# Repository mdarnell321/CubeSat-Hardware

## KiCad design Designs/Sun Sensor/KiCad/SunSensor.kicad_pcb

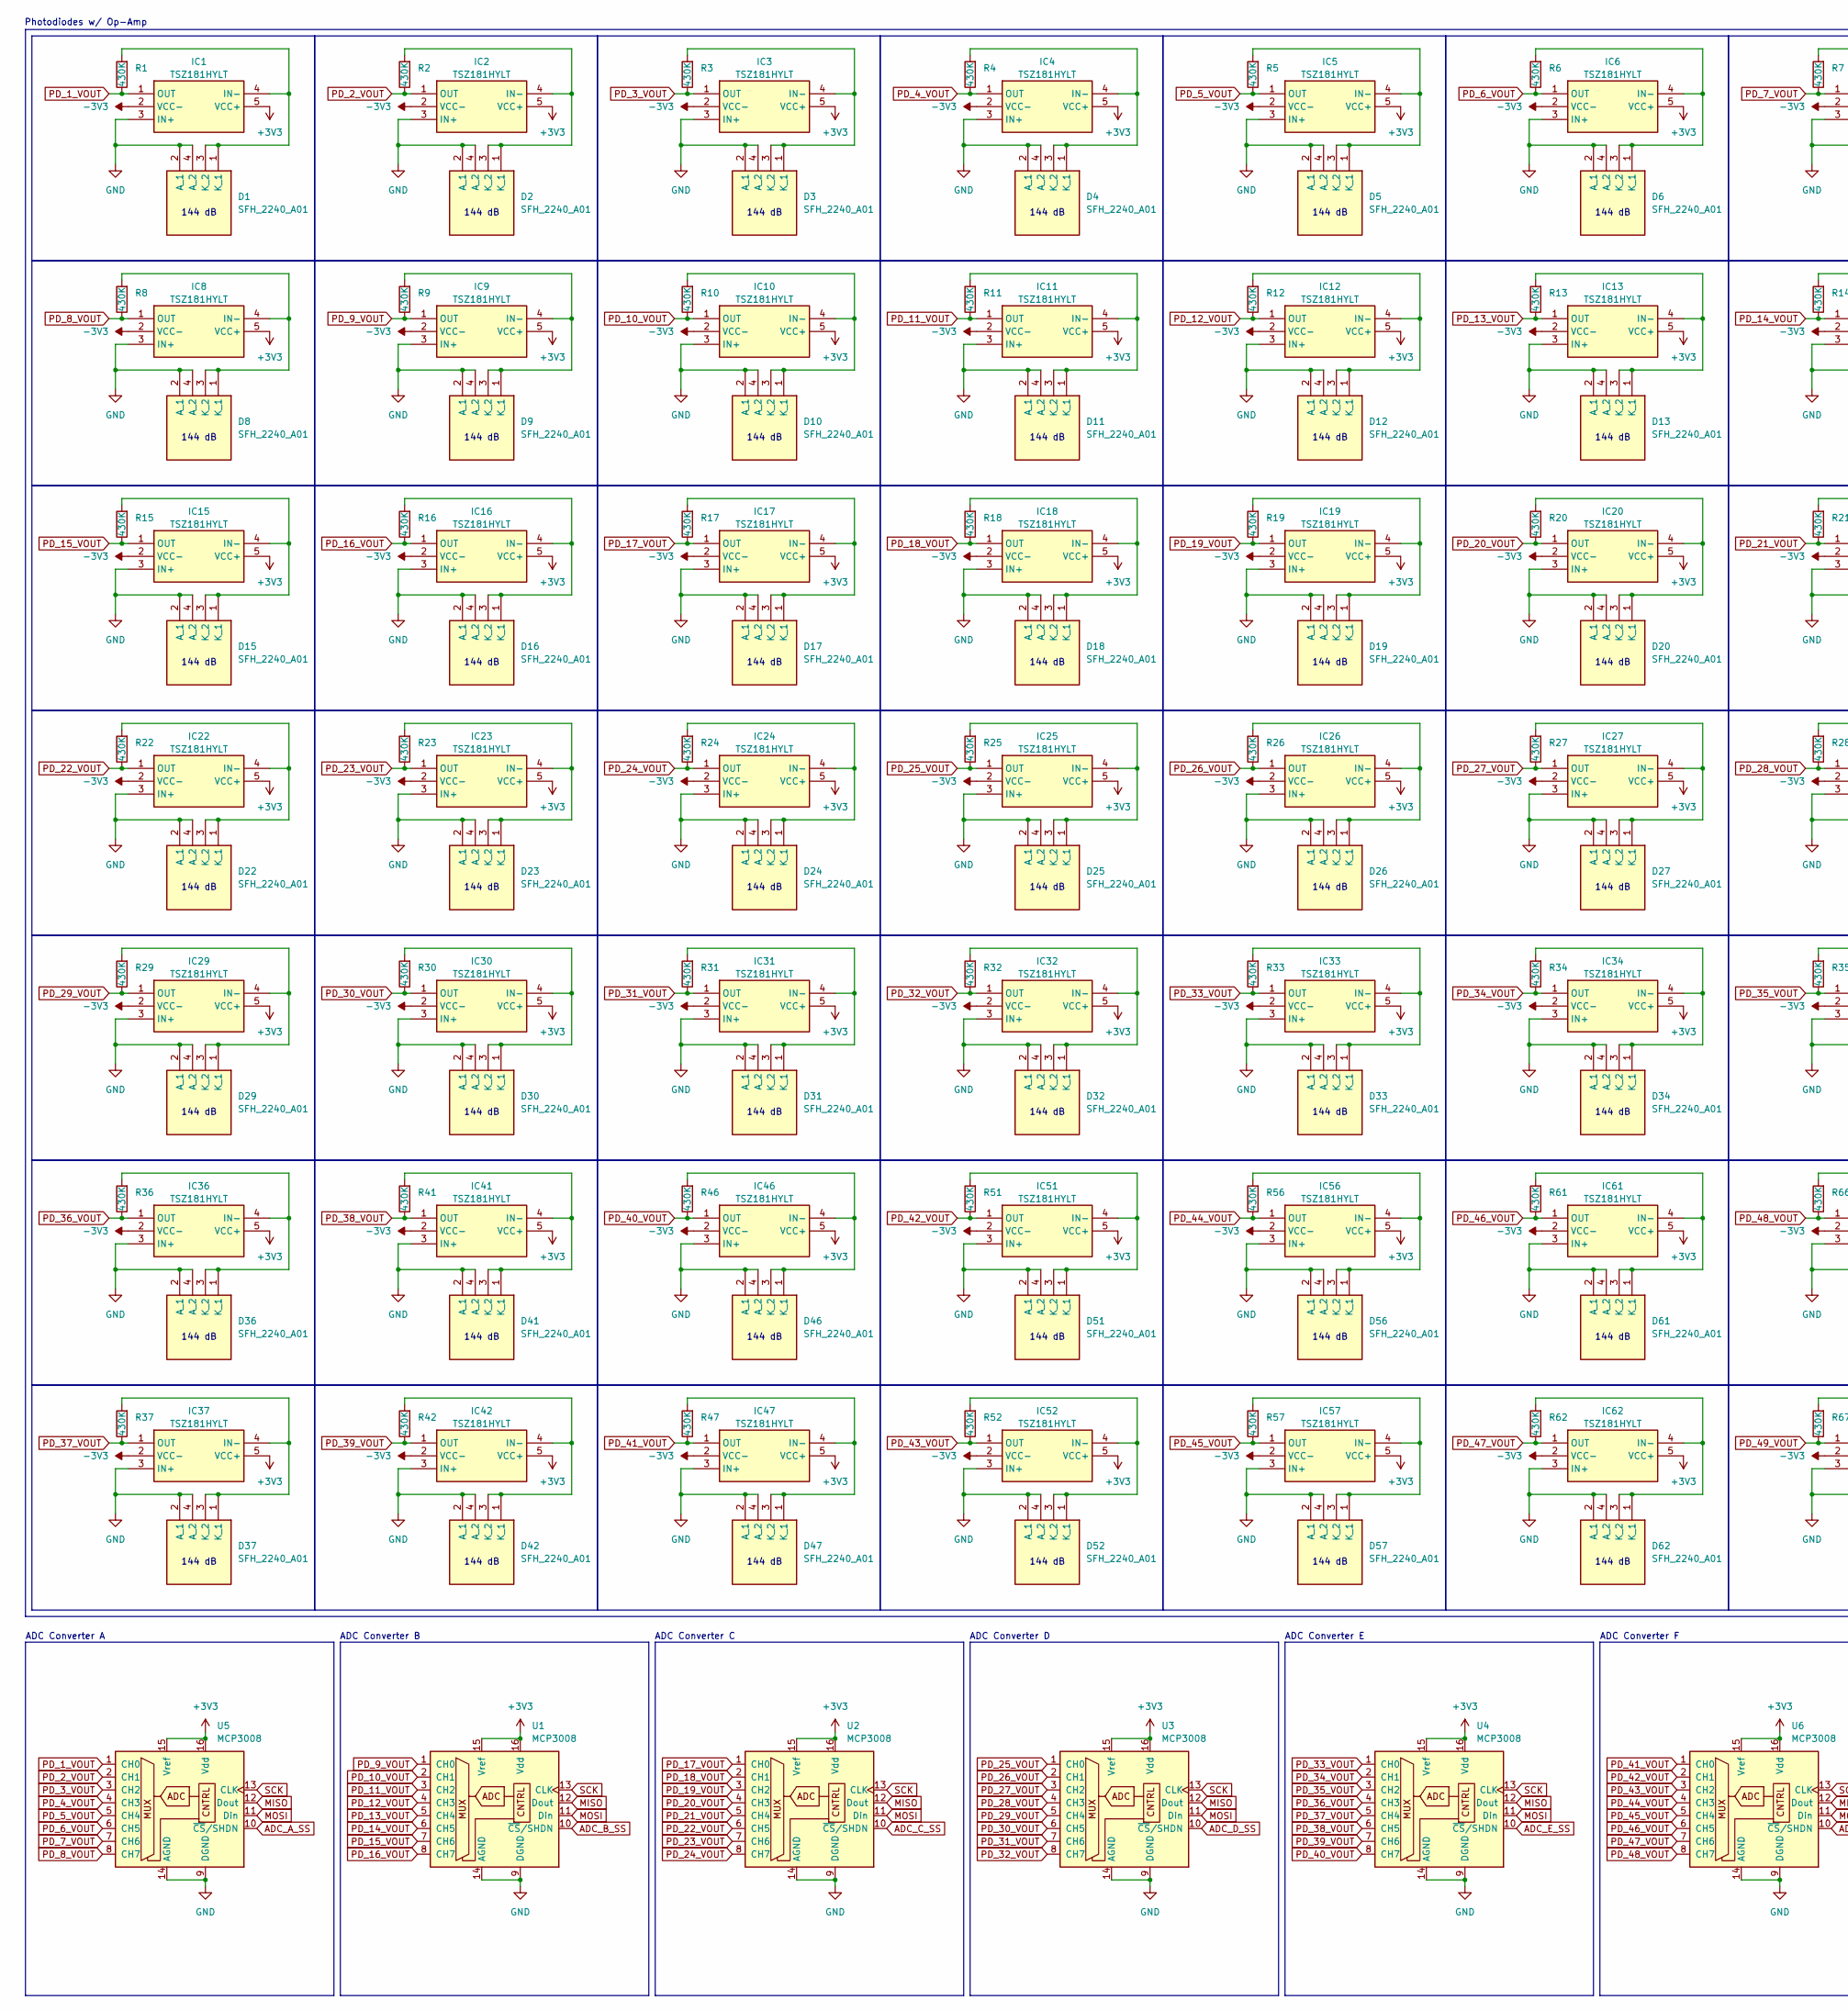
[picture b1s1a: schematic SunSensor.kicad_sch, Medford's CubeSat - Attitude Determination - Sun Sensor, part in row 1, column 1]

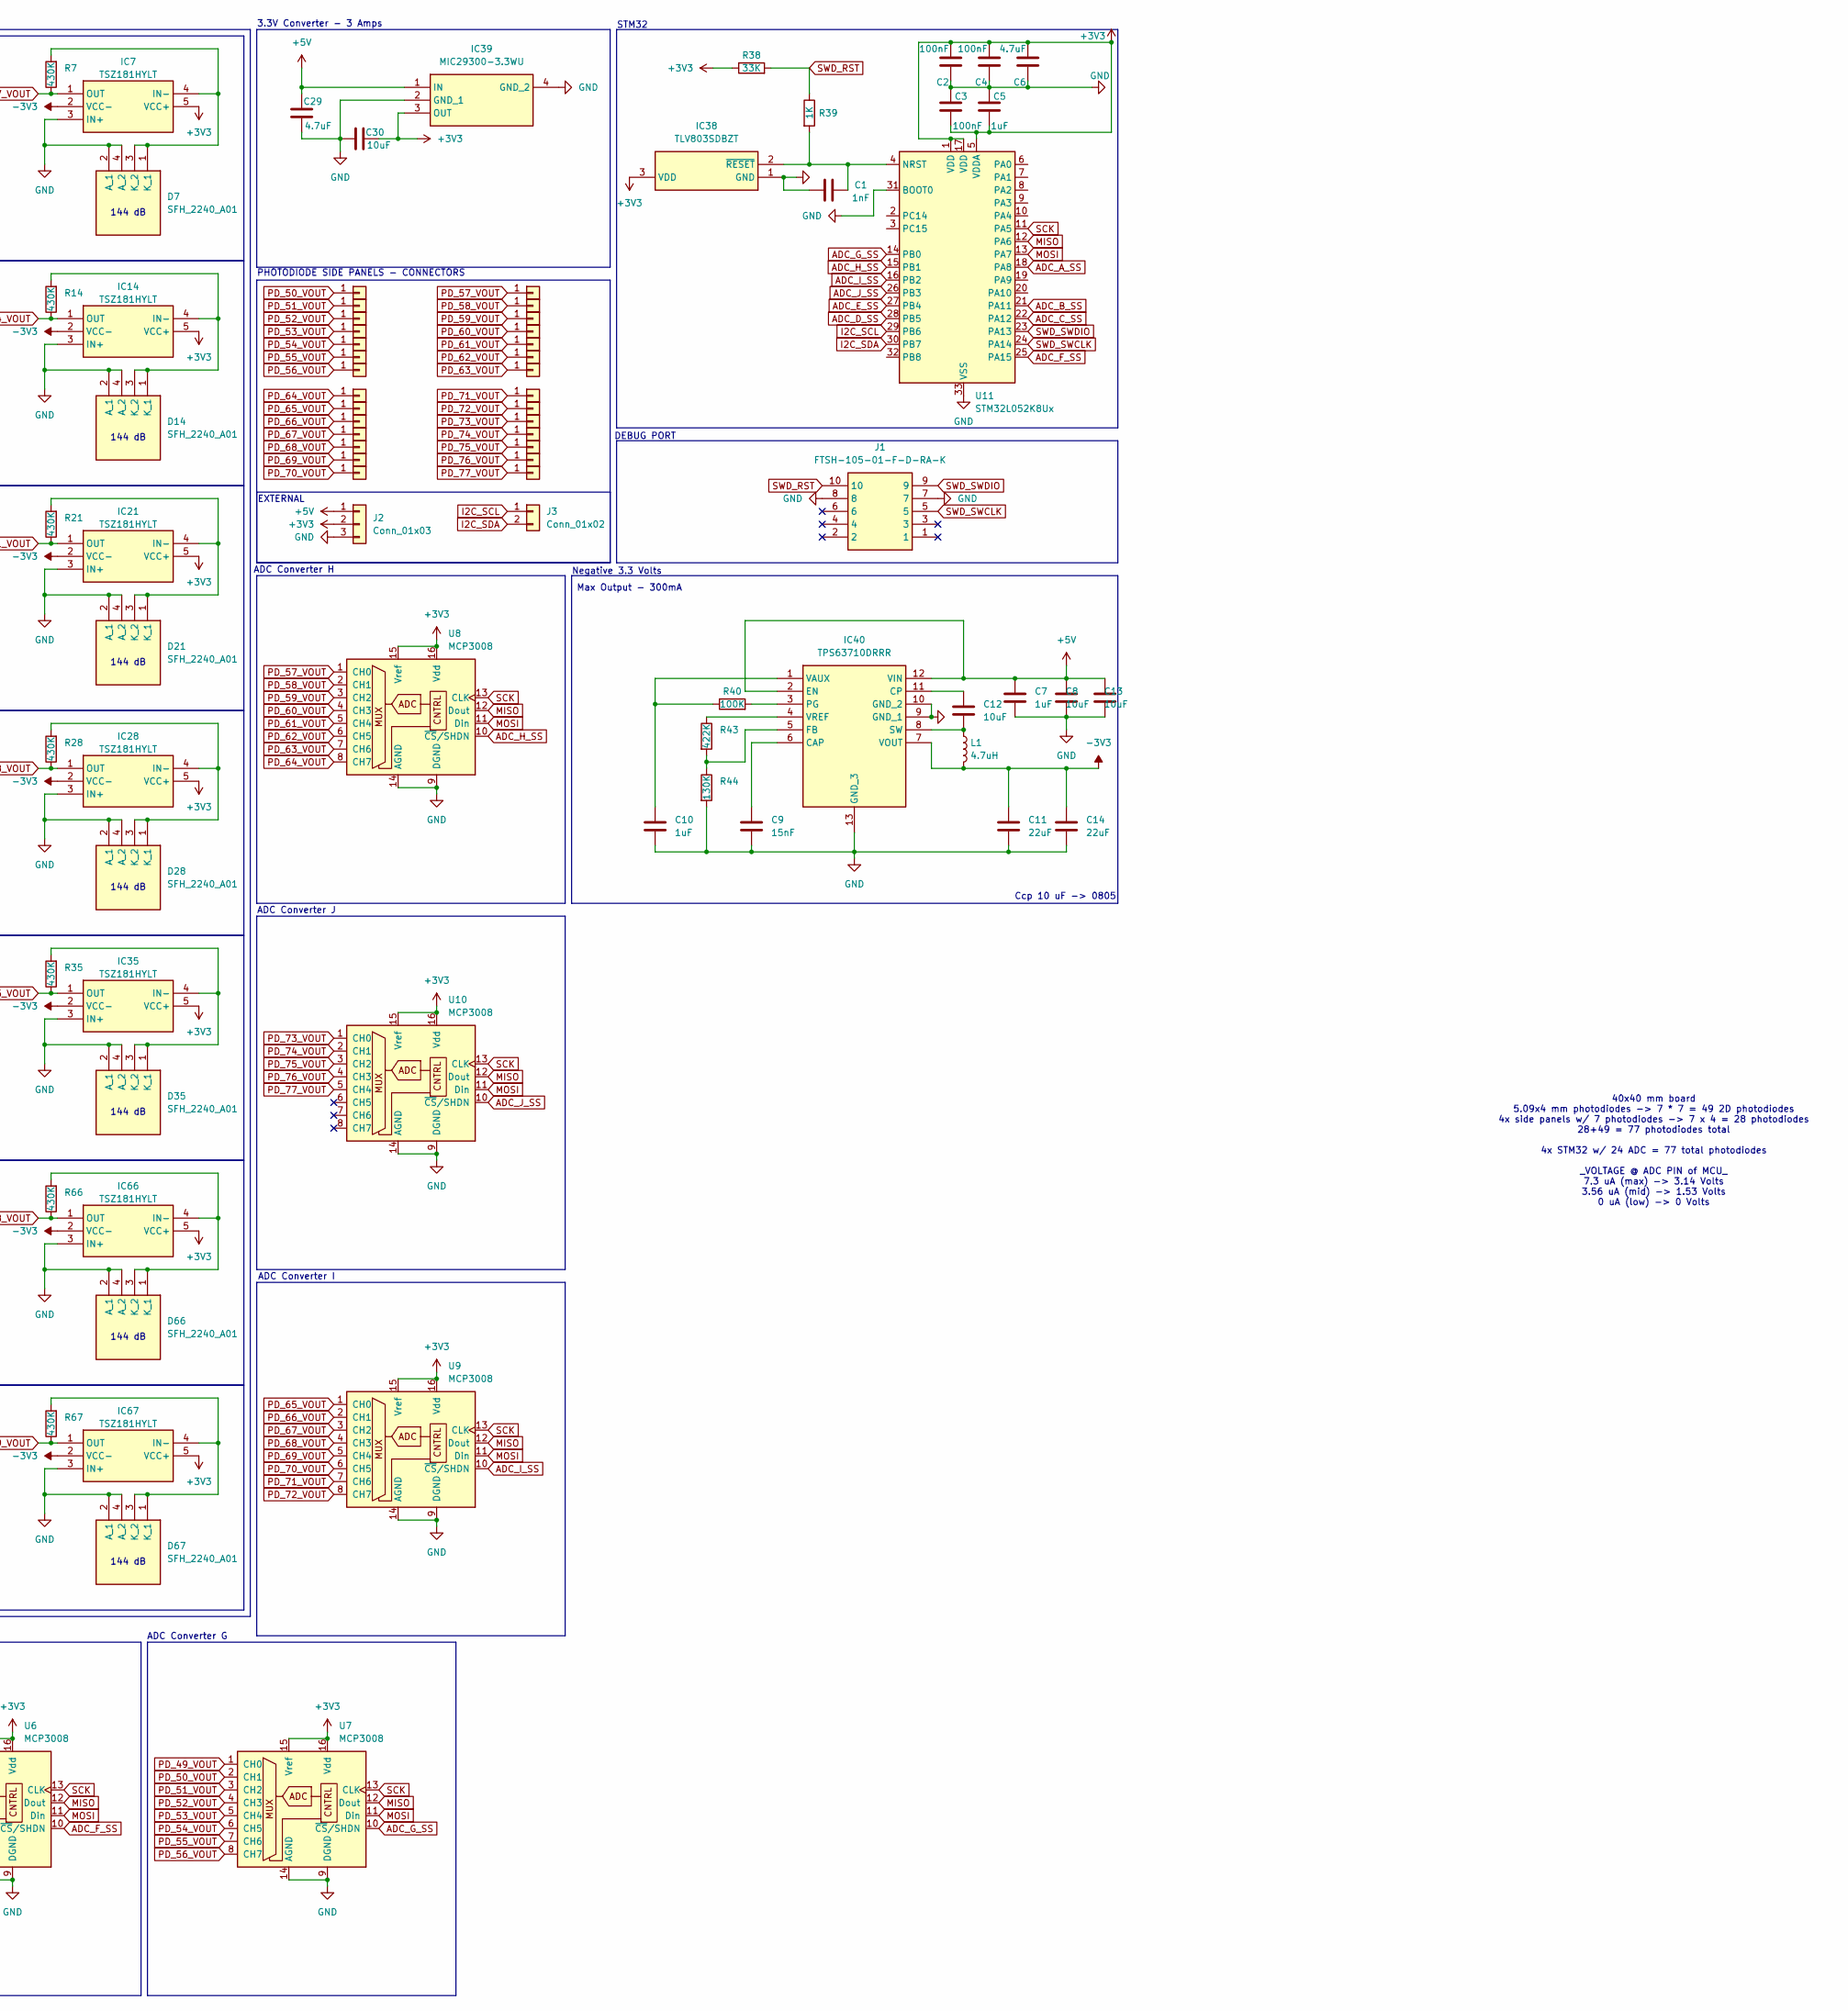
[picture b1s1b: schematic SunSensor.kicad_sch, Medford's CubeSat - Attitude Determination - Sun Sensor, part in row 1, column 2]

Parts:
C1: 1nF; C_0603_1608Metric
C2, C3, C4: 100nF; C_0603_1608Metric
C5, C7, C10: 1uF; C_0603_1608Metric
C6, C29: 4.7uF; C_0603_1608Metric
C8, C12, C13: 10uF; C_1206_3216Metric
C9: 15nF; C_01005_0402Metric
C11, C14: 22uF; C_0805_2012Metric
C30: 10uF; C_0603_1608Metric
D1, D2, D3, D4, D5, D6, D7, D8, D9, D10, D11, D12, D13, D14, D15, D16, D17, D18, D19, D20, D21, D22, D23, D24, D25, D26, D27, D28, D29, D30, D31, D32, D33, D34, D35, D36, D37, D41, D42, D46, D47, D51, D52, D56, D57, D61, D62, D66, D67: SFH_2240_A01; SFH2240A01; Mouser Part Number 720-SFH2240A01
IC1, IC2, IC3, IC4, IC5, IC6, IC7, IC8, IC9, IC10, IC11, IC12, IC13, IC14, IC15, IC16, IC17, IC18, IC19, IC20, IC21, IC22, IC23, IC24, IC25, IC26, IC27, IC28, IC29, IC30, IC31, IC32, IC33, IC34, IC35, IC36, IC37, IC41, IC42, IC46, IC47, IC51, IC52, IC56, IC57, IC61, IC62, IC66, IC67: TSZ181HYLT; SOT95P280X145-5N; Mouser Part Number 511-TSZ181HYLT
IC38: TLV803SDBZT; SOT95P237X95-3N; Mouser Part Number 595-TLV803SDBZT
IC39: MIC29300-3.3WU; MIC2930033WU; Mouser Part Number 998-MIC29300-3.3WU
IC40: TPS63710DRRR; SON50P300X300X80-13N-D; Mouser Part Number 595-TPS63710DRRR
J1: FTSH-105-01-F-D-RA-K; FTSH-105-XX-YYY-D-RA-K; Mouser Part Number 200-FTSH10501FDRAK
J2: Conn_01x03; PinHeader_1x03_P2.54mm_Vertical
J3: Conn_01x02; PinHeader_1x02_P2.54mm_Vertical
J4, J5, J6, J7, J8, J9, J10, J11, J12, J13, J14, J15, J16, J17, J18, J19, J20, J21, J22, J23, J24, J25, J26, J27, J28, J29, J30, J31: Conn_01x01; PinHeader_1x01_P2.54mm_Vertical
L1: 4.7uH; L_Vishay_IFSC-1515AH_4x4x1.8mm
R1, R2, R3, R4, R5, R6, R7, R8, R9, R10, R11, R12, R13, R14, R15, R16, R17, R18, R19, R20, R21, R22, R23, R24, R25, R26, R27, R28, R29, R30, R31, R32, R33, R34, R35, R36, R37, R41, R42, R46, R47, R51, R52, R56, R57, R61, R62, R66, R67: 430K; R_0603_1608Metric_Pad0.98x0.95mm_HandSolder
R38: 33K; R_0603_1608Metric
R39: 1K; R_0603_1608Metric
R40: 100K; R_0402_1005Metric
R43: 422K; R_0402_1005Metric
R44: 130K; R_0402_1005Metric
U1, U2, U3, U4, U5, U6, U7, U8, U9, U10: MCP3008; SOIC127P600X175-16N
U11: STM32L052K8Ux; QFN-32-1EP_5x5mm_P0.5mm_EP3.45x3.45mm

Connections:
+3V3: C2.2, C3.1, C4.2, C5.1, C6.2, C30.1, IC1.5 (VCC+), IC2.5 (VCC+), IC3.5 (VCC+), IC4.5 (VCC+), IC5.5 (VCC+), IC6.5 (VCC+), IC7.5 (VCC+), IC8.5 (VCC+), IC9.5 (VCC+), IC10.5 (VCC+), IC11.5 (VCC+), IC12.5 (VCC+), IC13.5 (VCC+), IC14.5 (VCC+), IC15.5 (VCC+), IC16.5 (VCC+), IC17.5 (VCC+), IC18.5 (VCC+), IC19.5 (VCC+), IC20.5 (VCC+), IC21.5 (VCC+), IC22.5 (VCC+), IC23.5 (VCC+), IC24.5 (VCC+), IC25.5 (VCC+), IC26.5 (VCC+), IC27.5 (VCC+), IC28.5 (VCC+), IC29.5 (VCC+), IC30.5 (VCC+), IC31.5 (VCC+), IC32.5 (VCC+), IC33.5 (VCC+), IC34.5 (VCC+), IC35.5 (VCC+), IC36.5 (VCC+), IC37.5 (VCC+), IC38.3 (VDD), IC39.3 (OUT), IC41.5 (VCC+), IC42.5 (VCC+), IC46.5 (VCC+), IC47.5 (VCC+), IC51.5 (VCC+), IC52.5 (VCC+), IC56.5 (VCC+), IC57.5 (VCC+), IC61.5 (VCC+), IC62.5 (VCC+), IC66.5 (VCC+), IC67.5 (VCC+), J2.2, R38.1, U1.15 (Vref), U1.16 (Vdd), U2.15 (Vref), U2.16 (Vdd), U3.15 (Vref), U3.16 (Vdd), U4.15 (Vref), U4.16 (Vdd), U5.15 (Vref), U5.16 (Vdd), U6.15 (Vref), U6.16 (Vdd), U7.15 (Vref), U7.16 (Vdd), U8.15 (Vref), U8.16 (Vdd), U9.15 (Vref), U9.16 (Vdd), U10.15 (Vref), U10.16 (Vdd), U11.1 (VDD), U11.5 (VDDA), U11.17 (VDD)
+5V: C7.1, C8.1, C13.1, C29.1, IC39.1 (IN), IC40.2 (EN), IC40.12 (VIN), J2.1
-3V3: C11.1, C14.1, IC1.2 (VCC-), IC2.2 (VCC-), IC3.2 (VCC-), IC4.2 (VCC-), IC5.2 (VCC-), IC6.2 (VCC-), IC7.2 (VCC-), IC8.2 (VCC-), IC9.2 (VCC-), IC10.2 (VCC-), IC11.2 (VCC-), IC12.2 (VCC-), IC13.2 (VCC-), IC14.2 (VCC-), IC15.2 (VCC-), IC16.2 (VCC-), IC17.2 (VCC-), IC18.2 (VCC-), IC19.2 (VCC-), IC20.2 (VCC-), IC21.2 (VCC-), IC22.2 (VCC-), IC23.2 (VCC-), IC24.2 (VCC-), IC25.2 (VCC-), IC26.2 (VCC-), IC27.2 (VCC-), IC28.2 (VCC-), IC29.2 (VCC-), IC30.2 (VCC-), IC31.2 (VCC-), IC32.2 (VCC-), IC33.2 (VCC-), IC34.2 (VCC-), IC35.2 (VCC-), IC36.2 (VCC-), IC37.2 (VCC-), IC40.7 (VOUT), IC41.2 (VCC-), IC42.2 (VCC-), IC46.2 (VCC-), IC47.2 (VCC-), IC51.2 (VCC-), IC52.2 (VCC-), IC56.2 (VCC-), IC57.2 (VCC-), IC61.2 (VCC-), IC62.2 (VCC-), IC66.2 (VCC-), IC67.2 (VCC-), L1.2
ADC_A_SS: U5.10 (~CS/SHDN), U11.18 (PA8)
ADC_B_SS: U1.10 (~CS/SHDN), U11.21 (PA11)
ADC_C_SS: U2.10 (~CS/SHDN), U11.22 (PA12)
ADC_D_SS: U3.10 (~CS/SHDN), U11.28 (PB5)
ADC_E_SS: U4.10 (~CS/SHDN), U11.27 (PB4)
ADC_F_SS: U6.10 (~CS/SHDN), U11.25 (PA15)
ADC_G_SS: U7.10 (~CS/SHDN), U11.14 (PB0)
ADC_H_SS: U8.10 (~CS/SHDN), U11.15 (PB1)
ADC_I_SS: U9.10 (~CS/SHDN), U11.16 (PB2)
ADC_J_SS: U10.10 (~CS/SHDN), U11.26 (PB3)
GND: C1.1, C2.1, C3.2, C4.1, C5.2, C6.1, C7.2, C8.2, C9.2, C10.2, C11.2, C13.2, C14.2, C29.2, C30.2, D1.2 (A_1), D1.4 (A_2), D2.2 (A_1), D2.4 (A_2), D3.2 (A_1), D3.4 (A_2), D4.2 (A_1), D4.4 (A_2), D5.2 (A_1), D5.4 (A_2), D6.2 (A_1), D6.4 (A_2), D7.2 (A_1), D7.4 (A_2), D8.2 (A_1), D8.4 (A_2), D9.2 (A_1), D9.4 (A_2), D10.2 (A_1), D10.4 (A_2), D11.2 (A_1), D11.4 (A_2), D12.2 (A_1), D12.4 (A_2), D13.2 (A_1), D13.4 (A_2), D14.2 (A_1), D14.4 (A_2), D15.2 (A_1), D15.4 (A_2), D16.2 (A_1), D16.4 (A_2), D17.2 (A_1), D17.4 (A_2), D18.2 (A_1), D18.4 (A_2), D19.2 (A_1), D19.4 (A_2), D20.2 (A_1), D20.4 (A_2), D21.2 (A_1), D21.4 (A_2), D22.2 (A_1), D22.4 (A_2), D23.2 (A_1), D23.4 (A_2), D24.2 (A_1), D24.4 (A_2), D25.2 (A_1), D25.4 (A_2), D26.2 (A_1), D26.4 (A_2), D27.2 (A_1), D27.4 (A_2), D28.2 (A_1), D28.4 (A_2), D29.2 (A_1), D29.4 (A_2), D30.2 (A_1), D30.4 (A_2), D31.2 (A_1), D31.4 (A_2), D32.2 (A_1), D32.4 (A_2), D33.2 (A_1), D33.4 (A_2), D34.2 (A_1), D34.4 (A_2), D35.2 (A_1), D35.4 (A_2), D36.2 (A_1), D36.4 (A_2), D37.2 (A_1), D37.4 (A_2), D41.2 (A_1), D41.4 (A_2), D42.2 (A_1), D42.4 (A_2), D46.2 (A_1), D46.4 (A_2), D47.2 (A_1), D47.4 (A_2), D51.2 (A_1), D51.4 (A_2), D52.2 (A_1), D52.4 (A_2), D56.2 (A_1), D56.4 (A_2), D57.2 (A_1), D57.4 (A_2), D61.2 (A_1), D61.4 (A_2), D62.2 (A_1), D62.4 (A_2), D66.2 (A_1), D66.4 (A_2), D67.2 (A_1), D67.4 (A_2), IC1.3 (IN+), IC2.3 (IN+), IC3.3 (IN+), IC4.3 (IN+), IC5.3 (IN+), IC6.3 (IN+), IC7.3 (IN+), IC8.3 (IN+), IC9.3 (IN+), IC10.3 (IN+), IC11.3 (IN+), IC12.3 (IN+), IC13.3 (IN+), IC14.3 (IN+), IC15.3 (IN+), IC16.3 (IN+), IC17.3 (IN+), IC18.3 (IN+), IC19.3 (IN+), IC20.3 (IN+), IC21.3 (IN+), IC22.3 (IN+), IC23.3 (IN+), IC24.3 (IN+), IC25.3 (IN+), IC26.3 (IN+), IC27.3 (IN+), IC28.3 (IN+), IC29.3 (IN+), IC30.3 (IN+), IC31.3 (IN+), IC32.3 (IN+), IC33.3 (IN+), IC34.3 (IN+), IC35.3 (IN+), IC36.3 (IN+), IC37.3 (IN+), IC38.1 (GND), IC39.2 (GND_1), IC39.4 (GND_2), IC40.9 (GND_1), IC40.10 (GND_2), IC40.13 (GND_3), IC41.3 (IN+), IC42.3 (IN+), IC46.3 (IN+), IC47.3 (IN+), IC51.3 (IN+), IC52.3 (IN+), IC56.3 (IN+), IC57.3 (IN+), IC61.3 (IN+), IC62.3 (IN+), IC66.3 (IN+), IC67.3 (IN+), J1.7, J1.8, J2.3, R44.2, U1.9 (DGND), U1.14 (AGND), U2.9 (DGND), U2.14 (AGND), U3.9 (DGND), U3.14 (AGND), U4.9 (DGND), U4.14 (AGND), U5.9 (DGND), U5.14 (AGND), U6.9 (DGND), U6.14 (AGND), U7.9 (DGND), U7.14 (AGND), U8.9 (DGND), U8.14 (AGND), U9.9 (DGND), U9.14 (AGND), U10.9 (DGND), U10.14 (AGND), U11.31 (BOOT0), U11.33 (VSS)
MISO: U1.12 (Dout), U2.12 (Dout), U3.12 (Dout), U4.12 (Dout), U5.12 (Dout), U6.12 (Dout), U7.12 (Dout), U8.12 (Dout), U9.12 (Dout), U10.12 (Dout), U11.12 (PA6)
MOSI: U1.11 (Din), U2.11 (Din), U3.11 (Din), U4.11 (Din), U5.11 (Din), U6.11 (Din), U7.11 (Din), U8.11 (Din), U9.11 (Din), U10.11 (Din), U11.13 (PA7)
unnamed: D1.1 (K_1), D1.3 (K_2), IC1.4 (IN-), R1.2
unnamed: D2.1 (K_1), D2.3 (K_2), IC2.4 (IN-), R2.2
unnamed: D3.1 (K_1), D3.3 (K_2), IC3.4 (IN-), R3.2
unnamed: D4.1 (K_1), D4.3 (K_2), IC4.4 (IN-), R4.2
unnamed: D5.1 (K_1), D5.3 (K_2), IC5.4 (IN-), R5.2
unnamed: D6.1 (K_1), D6.3 (K_2), IC6.4 (IN-), R6.2
unnamed: D7.1 (K_1), D7.3 (K_2), IC7.4 (IN-), R7.2
unnamed: D8.1 (K_1), D8.3 (K_2), IC8.4 (IN-), R8.2
unnamed: D9.1 (K_1), D9.3 (K_2), IC9.4 (IN-), R9.2
unnamed: D10.1 (K_1), D10.3 (K_2), IC10.4 (IN-), R10.2
unnamed: D11.1 (K_1), D11.3 (K_2), IC11.4 (IN-), R11.2
unnamed: D12.1 (K_1), D12.3 (K_2), IC12.4 (IN-), R12.2
unnamed: D13.1 (K_1), D13.3 (K_2), IC13.4 (IN-), R13.2
unnamed: D14.1 (K_1), D14.3 (K_2), IC14.4 (IN-), R14.2
unnamed: D15.1 (K_1), D15.3 (K_2), IC15.4 (IN-), R15.2
unnamed: D16.1 (K_1), D16.3 (K_2), IC16.4 (IN-), R16.2
unnamed: D17.1 (K_1), D17.3 (K_2), IC17.4 (IN-), R17.2
unnamed: D18.1 (K_1), D18.3 (K_2), IC18.4 (IN-), R18.2
unnamed: D19.1 (K_1), D19.3 (K_2), IC19.4 (IN-), R19.2
unnamed: D20.1 (K_1), D20.3 (K_2), IC20.4 (IN-), R20.2
unnamed: D21.1 (K_1), D21.3 (K_2), IC21.4 (IN-), R21.2
unnamed: D22.1 (K_1), D22.3 (K_2), IC22.4 (IN-), R22.2
unnamed: D23.1 (K_1), D23.3 (K_2), IC23.4 (IN-), R23.2
unnamed: D24.1 (K_1), D24.3 (K_2), IC24.4 (IN-), R24.2
unnamed: D25.1 (K_1), D25.3 (K_2), IC25.4 (IN-), R25.2
unnamed: D26.1 (K_1), D26.3 (K_2), IC26.4 (IN-), R26.2
unnamed: D27.1 (K_1), D27.3 (K_2), IC27.4 (IN-), R27.2
unnamed: D28.1 (K_1), D28.3 (K_2), IC28.4 (IN-), R28.2
unnamed: D29.1 (K_1), D29.3 (K_2), IC29.4 (IN-), R29.2
unnamed: D30.1 (K_1), D30.3 (K_2), IC30.4 (IN-), R30.2
unnamed: D31.1 (K_1), D31.3 (K_2), IC31.4 (IN-), R31.2
unnamed: D32.1 (K_1), D32.3 (K_2), IC32.4 (IN-), R32.2
unnamed: D33.1 (K_1), D33.3 (K_2), IC33.4 (IN-), R33.2
unnamed: D34.1 (K_1), D34.3 (K_2), IC34.4 (IN-), R34.2
unnamed: D35.1 (K_1), D35.3 (K_2), IC35.4 (IN-), R35.2
unnamed: D36.1 (K_1), D36.3 (K_2), IC36.4 (IN-), R36.2
unnamed: D37.1 (K_1), D37.3 (K_2), IC37.4 (IN-), R37.2
unnamed: D41.1 (K_1), D41.3 (K_2), IC41.4 (IN-), R41.2
unnamed: D42.1 (K_1), D42.3 (K_2), IC42.4 (IN-), R42.2
unnamed: D46.1 (K_1), D46.3 (K_2), IC46.4 (IN-), R46.2
unnamed: D47.1 (K_1), D47.3 (K_2), IC47.4 (IN-), R47.2
unnamed: D51.1 (K_1), D51.3 (K_2), IC51.4 (IN-), R51.2
unnamed: D52.1 (K_1), D52.3 (K_2), IC52.4 (IN-), R52.2
unnamed: D56.1 (K_1), D56.3 (K_2), IC56.4 (IN-), R56.2
unnamed: D57.1 (K_1), D57.3 (K_2), IC57.4 (IN-), R57.2
unnamed: D61.1 (K_1), D61.3 (K_2), IC61.4 (IN-), R61.2
unnamed: D62.1 (K_1), D62.3 (K_2), IC62.4 (IN-), R62.2
unnamed: D66.1 (K_1), D66.3 (K_2), IC66.4 (IN-), R66.2
unnamed: D67.1 (K_1), D67.3 (K_2), IC67.4 (IN-), R67.2
unnamed: C1.2, IC38.2 (~RESET), R39.2, U11.4 (NRST)
unnamed: C9.1, IC40.6 (CAP)
unnamed: C12.1, IC40.11 (CP)
unnamed: IC40.5 (FB), R43.2, R44.1
unnamed: IC40.3 (PG), R40.2
unnamed: C12.2, IC40.8 (SW), L1.1
unnamed: C10.1, IC40.1 (VAUX), R40.1
unnamed: IC40.4 (VREF), R43.1
PD_1_VOUT: IC1.1 (OUT), R1.1, U5.1 (CH0)
PD_2_VOUT: IC2.1 (OUT), R2.1, U5.2 (CH1)
PD_3_VOUT: IC3.1 (OUT), R3.1, U5.3 (CH2)
PD_4_VOUT: IC4.1 (OUT), R4.1, U5.4 (CH3)
PD_5_VOUT: IC5.1 (OUT), R5.1, U5.5 (CH4)
PD_6_VOUT: IC6.1 (OUT), R6.1, U5.6 (CH5)
PD_7_VOUT: IC7.1 (OUT), R7.1, U5.7 (CH6)
PD_8_VOUT: IC8.1 (OUT), R8.1, U5.8 (CH7)
PD_9_VOUT: IC9.1 (OUT), R9.1, U1.1 (CH0)
PD_10_VOUT: IC10.1 (OUT), R10.1, U1.2 (CH1)
PD_11_VOUT: IC11.1 (OUT), R11.1, U1.3 (CH2)
PD_12_VOUT: IC12.1 (OUT), R12.1, U1.4 (CH3)
PD_13_VOUT: IC13.1 (OUT), R13.1, U1.5 (CH4)
PD_14_VOUT: IC14.1 (OUT), R14.1, U1.6 (CH5)
PD_15_VOUT: IC15.1 (OUT), R15.1, U1.7 (CH6)
PD_16_VOUT: IC16.1 (OUT), R16.1, U1.8 (CH7)
PD_17_VOUT: IC17.1 (OUT), R17.1, U2.1 (CH0)
PD_18_VOUT: IC18.1 (OUT), R18.1, U2.2 (CH1)
PD_19_VOUT: IC19.1 (OUT), R19.1, U2.3 (CH2)
PD_20_VOUT: IC20.1 (OUT), R20.1, U2.4 (CH3)
PD_21_VOUT: IC21.1 (OUT), R21.1, U2.5 (CH4)
PD_22_VOUT: IC22.1 (OUT), R22.1, U2.6 (CH5)
PD_23_VOUT: IC23.1 (OUT), R23.1, U2.7 (CH6)
PD_24_VOUT: IC24.1 (OUT), R24.1, U2.8 (CH7)
PD_25_VOUT: IC25.1 (OUT), R25.1, U3.1 (CH0)
PD_26_VOUT: IC26.1 (OUT), R26.1, U3.2 (CH1)
PD_27_VOUT: IC27.1 (OUT), R27.1, U3.3 (CH2)
PD_28_VOUT: IC28.1 (OUT), R28.1, U3.4 (CH3)
PD_29_VOUT: IC29.1 (OUT), R29.1, U3.5 (CH4)
PD_30_VOUT: IC30.1 (OUT), R30.1, U3.6 (CH5)
PD_31_VOUT: IC31.1 (OUT), R31.1, U3.7 (CH6)
PD_32_VOUT: IC32.1 (OUT), R32.1, U3.8 (CH7)
PD_33_VOUT: IC33.1 (OUT), R33.1, U4.1 (CH0)
PD_34_VOUT: IC34.1 (OUT), R34.1, U4.2 (CH1)
PD_35_VOUT: IC35.1 (OUT), R35.1, U4.3 (CH2)
PD_36_VOUT: IC36.1 (OUT), R36.1, U4.4 (CH3)
PD_37_VOUT: IC37.1 (OUT), R37.1, U4.5 (CH4)
PD_38_VOUT: IC41.1 (OUT), R41.1, U4.6 (CH5)
PD_39_VOUT: IC42.1 (OUT), R42.1, U4.7 (CH6)
PD_40_VOUT: IC46.1 (OUT), R46.1, U4.8 (CH7)
PD_41_VOUT: IC47.1 (OUT), R47.1, U6.1 (CH0)
PD_42_VOUT: IC51.1 (OUT), R51.1, U6.2 (CH1)
PD_43_VOUT: IC52.1 (OUT), R52.1, U6.3 (CH2)
PD_44_VOUT: IC56.1 (OUT), R56.1, U6.4 (CH3)
PD_45_VOUT: IC57.1 (OUT), R57.1, U6.5 (CH4)
PD_46_VOUT: IC61.1 (OUT), R61.1, U6.6 (CH5)
PD_47_VOUT: IC62.1 (OUT), R62.1, U6.7 (CH6)
PD_48_VOUT: IC66.1 (OUT), R66.1, U6.8 (CH7)
PD_49_VOUT: IC67.1 (OUT), R67.1, U7.1 (CH0)
PD_50_VOUT: J25.1, U7.2 (CH1)
PD_51_VOUT: J26.1, U7.3 (CH2)
PD_52_VOUT: J27.1, U7.4 (CH3)
PD_53_VOUT: J28.1, U7.5 (CH4)
PD_54_VOUT: J29.1, U7.6 (CH5)
PD_55_VOUT: J30.1, U7.7 (CH6)
PD_56_VOUT: J31.1, U7.8 (CH7)
PD_57_VOUT: J18.1, U8.1 (CH0)
PD_58_VOUT: J19.1, U8.2 (CH1)
PD_59_VOUT: J20.1, U8.3 (CH2)
PD_60_VOUT: J21.1, U8.4 (CH3)
PD_61_VOUT: J22.1, U8.5 (CH4)
PD_62_VOUT: J23.1, U8.6 (CH5)
PD_63_VOUT: J24.1, U8.7 (CH6)
PD_64_VOUT: J4.1, U8.8 (CH7)
PD_65_VOUT: J7.1, U9.1 (CH0)
PD_66_VOUT: J9.1, U9.2 (CH1)
PD_67_VOUT: J10.1, U9.3 (CH2)
PD_68_VOUT: J11.1, U9.4 (CH3)
PD_69_VOUT: J12.1, U9.5 (CH4)
PD_70_VOUT: J13.1, U9.6 (CH5)
PD_71_VOUT: J5.1, U9.7 (CH6)
PD_72_VOUT: J6.1, U9.8 (CH7)
PD_73_VOUT: J8.1, U10.1 (CH0)
PD_74_VOUT: J14.1, U10.2 (CH1)
PD_75_VOUT: J15.1, U10.3 (CH2)
PD_76_VOUT: J16.1, U10.4 (CH3)
PD_77_VOUT: J17.1, U10.5 (CH4)
SCK: U1.13 (CLK), U2.13 (CLK), U3.13 (CLK), U4.13 (CLK), U5.13 (CLK), U6.13 (CLK), U7.13 (CLK), U8.13 (CLK), U9.13 (CLK), U10.13 (CLK), U11.11 (PA5)
SWD_RST: J1.10, R38.2, R39.1
SWD_SWCLK: J1.5, U11.24 (PA14)
SWD_SWDIO: J1.9, U11.23 (PA13)
UART_RX: J3.1, U11.20 (PA10), U11.29 (PB6)
UART_TX: J3.2, U11.19 (PA9), U11.30 (PB7)

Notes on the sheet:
ADC Converter A
144 dB
Negative 3.3 Volts
ADC Converter E
ADC Converter D
ADC Converter C
Max Output - 300mA
EXTERNAL
ADC Converter I
ADC Converter B
Photodiodes w/ Op-Amp
STM32
3.3V Converter - 3 Amps
ADC Converter H
ADC Converter J
ADC Converter F
ADC Converter G
40x40 mm board 5.09x4 mm photodiodes -> 7 * 7 = 49 2D photodiodes 4x side panels w/ 7 photodiodes -> 7 x 4 = 28 photodiodes 28+49 = 77 photodiodes total 4x STM32 w/ 24 ADC = 77 total photodiodes _VOLTAGE @ ADC PIN of MCU_ 7.3 uA (max) -> 3.14 Volts 3.56 uA (mid) -> 1.53 Volts 0 uA (low) -> 0 Volts
DEBUG PORT
PHOTODIODE SIDE PANELS - CONNECTORS
Ccp 10 uF -> 0805

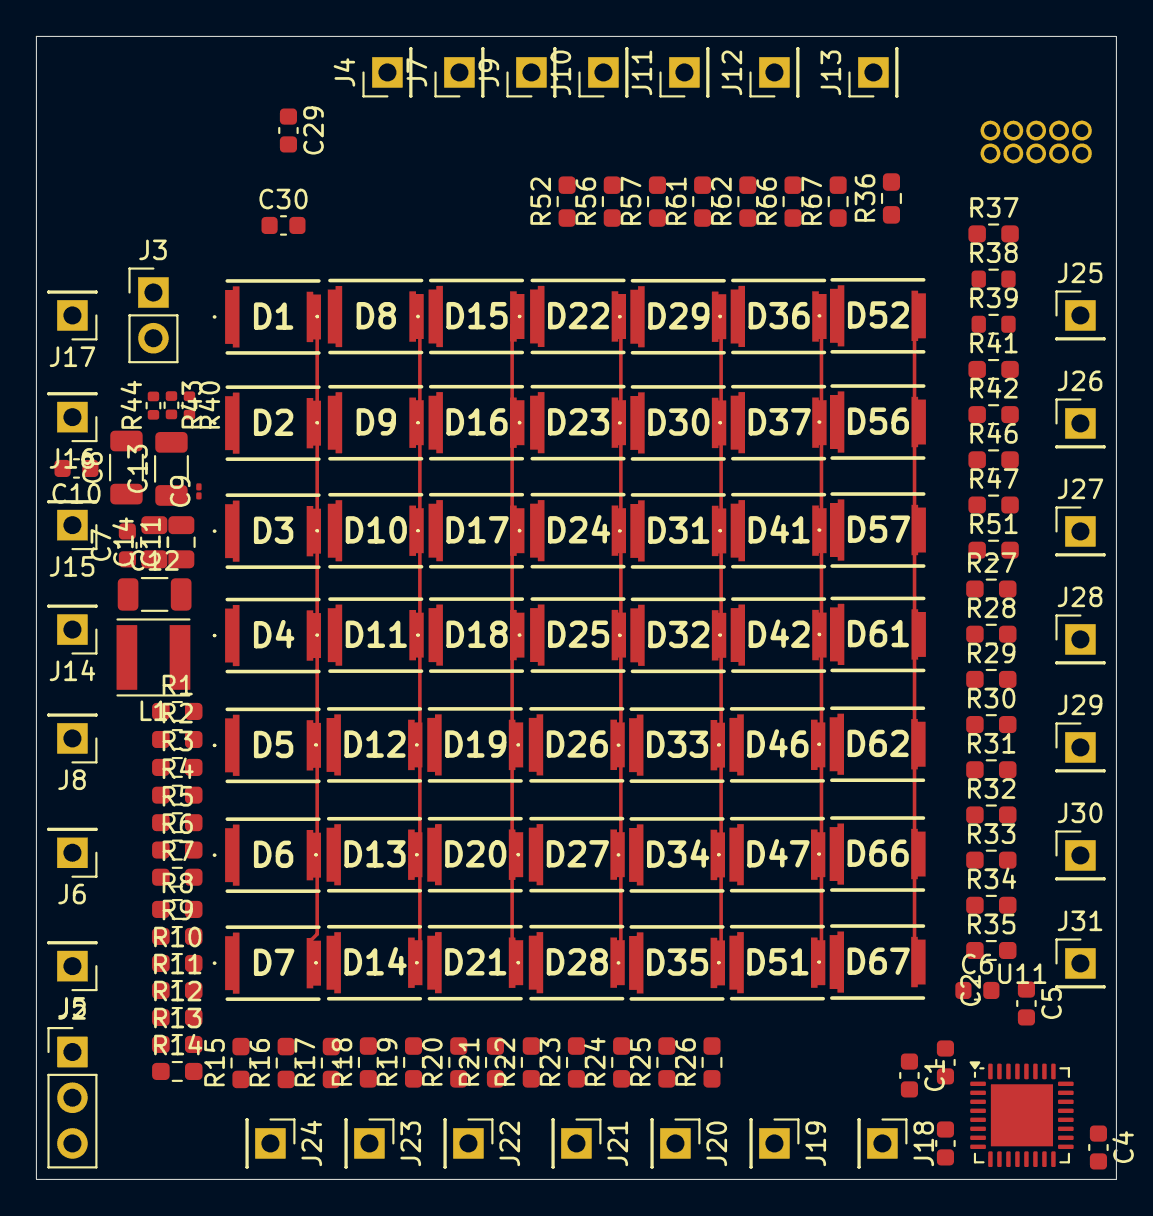
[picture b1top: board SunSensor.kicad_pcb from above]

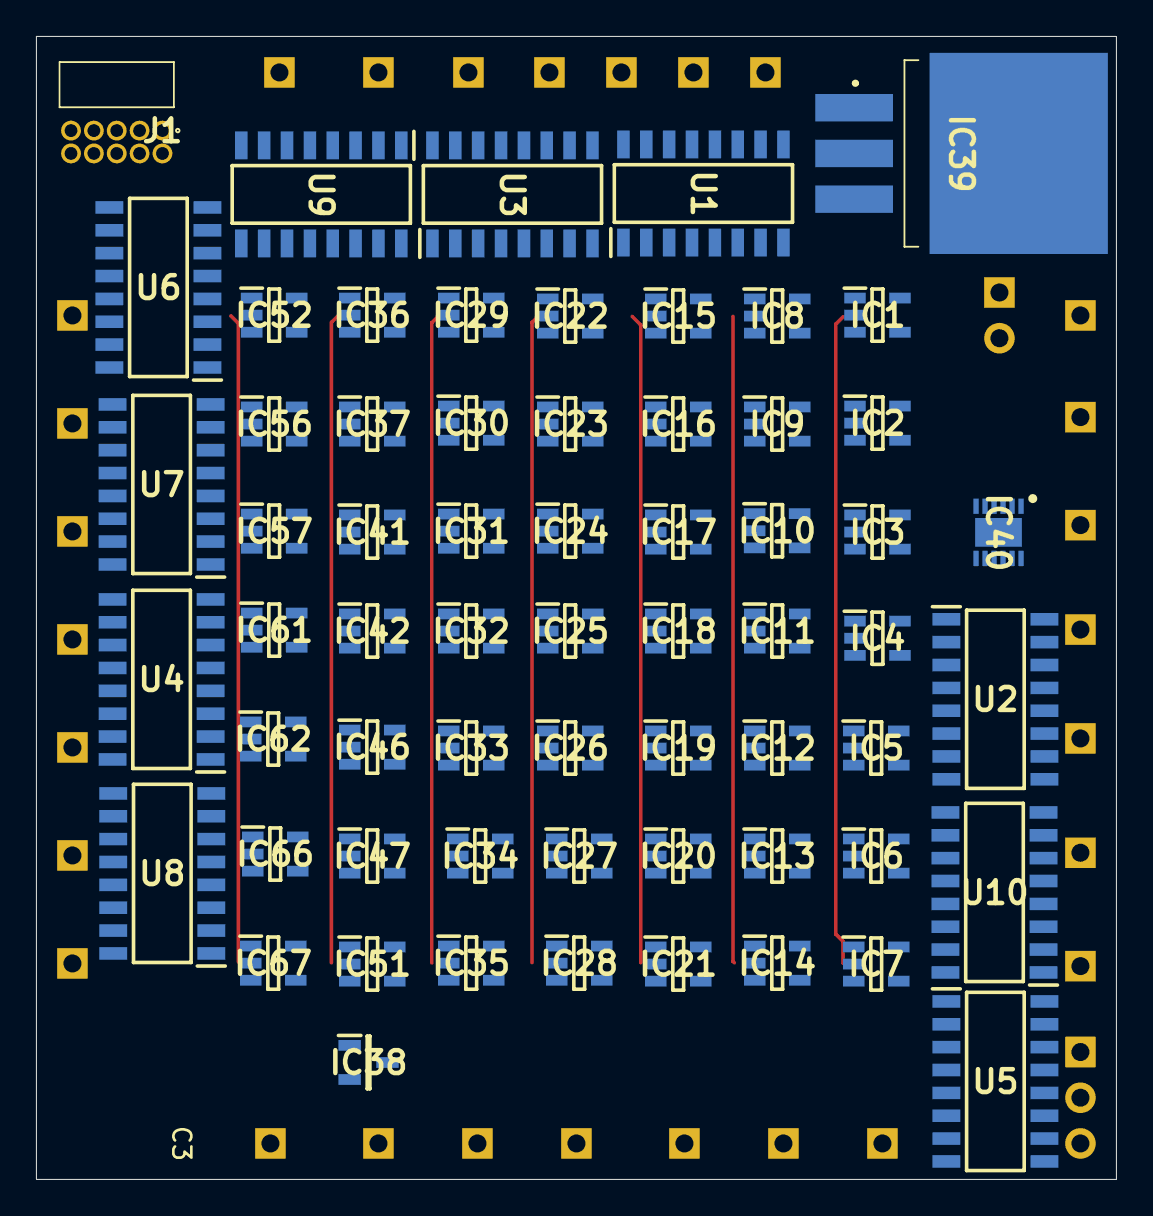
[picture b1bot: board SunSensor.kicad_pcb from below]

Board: 4 copper layers, 60.0 x 63.5 mm, 214 parts (63 on the bottom side), 156 nets.

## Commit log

2025-11-14 first
